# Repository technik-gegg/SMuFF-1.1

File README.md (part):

# Welcome to the SMuFF project

Here's the official firmware package for the **S**mart **Mu**lti **F**ilament **F**eeder, as published on [Printables](https://www.printables.com/de/model/194737-smuff-v6-smart-multi-filament-feeder-with-bondtech) and [Thingiverse](https://www.thingiverse.com/thing:3431438). Read the full story on how it came to life on my official [SMuFF homepage](https://sites.google.com/view/the-smuff/).

If you like this project and find it useful, you may consider [donating](https://sites.google.com/view/the-smuff/downloads/assembly-manual#h.m5ewgcp0jfk6).

To use this firmware, you have to [compile it](https://sites.google.com/view/the-smuff/how-to/tutorials/compile-the-firmware?authuser=0) and flash it to one of these (already supported) controller boards:

| Board |  |
|------------|-----|
| Bigtreetech [SKR mini E3 V3.0](https://www.biqu.equipment/products/bigtreetech-skr-mini-e3-v2-0-32-bit-control-board-for-ender-3) |**recommended** |
| Bigtreetech [SKR mini E3-DIP V1.1](https://www.biqu.equipment/products/bigtreetech-skr-e3-dip-v1-0-motherboard-for-ender-3)||
| Bigtreetech [SKR mini E3 V2.0](https://www.biqu.equipment/products/bigtreetech-skr-mini-e3-v2-0-32-bit-control-board-integrated-tmc2209-uart-for-ender-4) ||
| Bigtreetech [SKR mini V1.1](https://www.biqu.equipment/collections/control-board/products/bigtreetech-skr-mini-v1-1-motherboard-32-bit-arm-equipped-with-tmc2208-v2-1-tmc2130-spi-driver-stepstick-for-3d-printer-desktop?variant=20361870377058)||

The Bigtreetech SKR mini series boards are very small and yet powerful because of the 32-Bit STM Microcontroller Unit.

Of course, this firmware can also be configured to run on any other controller board, as long as it meets the specifications. Although you might be able to utilize older 8 bit boards, I don't recommended it - you'll most probably run out of memory (Flash/RAM) very soon. I recommend using a 32 bit controller board instead.
Make sure your board of choice has at least **256K** of Flash memory, **48K** of (S)RAM and all other components needed, which are at least:

+ two stepper motor drivers (sockets)
+ two endstop connectors
+ one servo connector (or two spare I/O pins for Software-I2C)
+ an onboard SD-Card
+ one spare serial port (USB or TTL)
+ a 128 x 64 pixel display connector
+ a rotary encoder connector

Simply create a new build environment in your **platformio.ini** and adopt the settings according to your controllers hardware in your custom **pins.h** file.

The configuration files **\*.json** and **debug.txt** have to be copied into the root folder of your SD-Card for the controller board. Hence, changing runtime parameters doesn't require recompiling the firmware. Just edit the settings from within the built-in menus or the [WebInterface](https://github.com/technik-gegg/SMuFF-WI), save them and reboot.

I've added the option to run GCode scripts for automated testing of your hardware.
In the **test** folder you'll find some sample scripts. Copy the folder over to your SD-Card and pick a script from within the menu to start the test run. Once started, the test will run infinitelly until you stop it.
Each test result will be displayed on the LCD and also sent to the log serial port (which is the USB port, if not defined otherwise).

For more information about building the SMuFF and some more detailed stuff, head over to my official [SMuFF homepage](https://sites.google.com/view/the-smuff/) or to my [Discord server](https://discord.com/invite/BzZ3rBf).

---

## Credit where credit is due

A special thanks to the folks who have created the following (Arduino) libraries, on which the SMuFF firmware builds upon:

+ [Adafruit](https://github.com/technik-gegg/Adafruit-PWM-Servo-Driver-Library.git) for the PWM Servo library
+ [Benoît Blanchon](https://github.com/bblanchon/ArduinoJson.git) for the Arduino JSON library
+ [Bill Greinman](https://github.com/greiman/SdFat) for the SD-Card library
+ [Oliver Kraus](https://github.com/olikraus/U8G2_Arduino.git) for the U8G2 display library
+ [teemuatlut](https://github.com/teemuatlut/TMCStepper) for the TMC-Stepper library
+ [the creators of the](https://github.com/technik-gegg/SoftWireSTM32/) SoftWireSTM32 library
+ [Tom Schimansky](https://github.com/TomSchimansky/CustomTkinter) for the Custom Tkinter Python package
+ [Akash Bora](https://github.com/Akascape) for the CTkMessagebox and CTkToolTip packages

---

## Recent changes

**3.25** - minor fixes/changes

+ restricted scanning of the I2C bus to valid slave addresses (0-7 and 120-127 are reserved addresses). Although this didn't cause any error yet, it could have caused some unwanted effects in the future.
+ added a new option to route debug messages to other than the default Serial 2 (a.k.a. TFT-Header): Create a file in the root folder of the SD-Card named:
  + **dbg2usb.txt** for Serial 0 (a.k.a. USB)
  + **dbg2exp.txt** for Serial 1
  + **dbg2oth.txt** for Serial 3

   **Keep in mind:** These files need no content. Not every port (except USB) is available on every board, it depends on board and configuration. To reset sending debug messages to default Serial 2, delete or rename the file.
+ added the **Adafruit Stepper + DC Motor FeatherWing** board as a 2nd option for the Spool-Rewinder controller. To use it, you have to define **USE_SPOOLMOTOR_FEATHERWING** in addition to **USE_SPOOLMOTOR** in the *config_defaults* and/or tick the according option in the *Firmware Build Configurator*.

**3.24** - added new "Firmware-Build Configurator"

+ made the build configuration easier by adding a custom dialog (Python/Ctk). Now, the *PROJECT TASKS* treeview only contains the basic build environments for each supported controller. Everything else can now be configured right after clicking on the **Build** task using this dialog:

This is by far more convenient than parsing through the *platformio.ini* or trying to find the build environment you want.
Tooltips will show up when hovering over the checkboxes, which briefly explain why you would use this option.
After the build you'll find a **readme-build.txt** file in the output folder, listing the options that have been set for this particular build.
To define a set of **personalized default settings** depending on the controller used, one can list them under the *config_defaults* section in *platformio.ini*.
*Please be aware that for using this feature, PlatformIO needs to install some Python packages once. This happens automatically at your very first build.*
+ updated SdFat library reference to 2.2.0
+ added the option to use the "old" clock settings (those recommended by STM) for the SKR E3 V3.0 board instead of the new ones introduced in version 3.23.
+ added a couple more debug messages while the firmware is being initialized.

**3.23** - bugfix, Motorized Spool Rewinder option added

+ fixed the bug that caused some (newer) SKR E3 V3.0 boards not being recognized (enumerated) when connected via USB.
+ added **_SPM** build environments, which allow utilizing the [Motorized Spool Rewinder](https://sites.google.com/view/the-smuff/how-to/build/the-spool-rewinder). To use this option, you have to copy the *help* and *menus* folders to your SMuFFs SD-Card. Also, please notice the added content in **MATERIALS.json**.
+ added GCodes **M3**, **M4** and **M5** to allow controlling the spool motors of the *Motorized Spool Rewinder*.

**3.22** - reorganized Build Environments

+ reorganized Build Environments as announced in 3.21.
.
+ added include of <stdint.h> to SMuFF.h, since latest builds seem to fail.

**3.21** - some changes based on the previous release

+ reworked the Build Environments in **platformio.ini**
 Since the **SKR E3 V3.0** has become the most dominant contoller board and the others are getting more and more outdated, I've decided to get rid of some of the Build Environments for "older boards" and add all the possible permutations for the E3 V3.0 instead. The suffixes are meant to be self-explanatory but as a hint: **NPX** means NeoPixels (on tools), **MS** means Multiservo and **DDE** means Direct Drive Extruder.
 Here's what the *PROJECT TASKS* treeview in VSCode now looks like:
 
 Simply open the Build Enviroment that matches your setup and click on "Build".
 Outdated Build Environments are still contained in the ini-file but need to be un-commented in order to make them show up in the *PROJECT TASKS* treeview.
+ the (FYSECT / BTT / MKS) **MiniPanel 12864 V2.1** display has become the default option now. It's the cheapest and easiest to source display, so I declared it the "standard".
+ while playing around with the new behaviour of **USE_NUM_PIXELS** introduced in the previous release, I figured, it's far easier to have the number of LEDs configurable at runtime and thus, I've moved it to the SMuFF configuration file. Hence, this definition is now gone from the platformio.ini!
When you update to this version, please keep in mind to also copy the new **display.mnu** and **m205.txt** to your SMuFF's SD-Card, into the folders *menu* and *help* accordingly.
+ I also found an unpleasant but logical behavior in the *Marquee* animation when more than 7 LEDs are in use: It skips LEDs because on the beatsin() calculation and BPM settings, so I fixed that.
+ while I was at it, I also added two new Idle-Animations: Rainbow and Cylone. Thus, you need to copy the **anim-type.opt** to the *options* folder as well. Then pick the one that you fancy the most from the *Display menu*.

**3.20** - small feature change

+ corrected the behaviour of the **USE_NUM_PIXELS** definition in *platformio.ini*. This defines how many **NeoPixel LEDs** one plans to use for one tool (which usually is: "1 LED per tool").
This feature comes in handy when you're using a NeoPixel strip with a higher density. The "standard" NeoPixel strips come with a density of 60 LEDs/meter but they're also available in 30, 72, 96, 144, 240 or even 332 LEDs/m.
It turned out, that on strips with **144 LEDs/m** the LED spacing is around 7mm (i.e. 1000/144 = 6.94), which corresponds to 3 LEDs for 21mm! Coincidentally, this is also the exact width of one Filament-Guide. Hence, using a 144 LED/m strip saves you from the tedious job of cutting a strip and re-soldering the LEDs in order to get them into the right position. Simply use a longer strip (3 LEDs * number_of_tools) and set **USE_NUM_PIXELS** to 3 before compiling the firmware.

**3.19** - bug fix

+ fixed bug in Selector homing. When homed, SMuFF wasn't able to select tools because the Selector endstop was still triggering.

**3.18** - minor bug fix

+ fixed bug in displaying menu items

**3.17** - minor bug fixes / optimizations

+ fixed bug in platformio.ini for SKR Mini environment.
+ fixed bug in *NeoPixels on Tools*, if more than 5 tools are being used. Init of the NeoPixels happened before the Config was read and hence the count of tools/NeoPixels was incorrect.
+ optimized code for the steppers (*ZStepperLib*) yet again. The *isrStepperTimerHandler()* method now has an overall runtime of about **15uS** on a **STM32F1** MCU running at 72MHz.
+ changed some methods in timers.h/timers.cpp in order to shave off some microseconds in processing time.
+ fixed bug in synchronous movement of the steppers. Feeder stepper wasn't moving at the same pace as the DDE Feeder.
+ changed the USB signature to **STMicroelectronics SMuFF 3.x**. This way it's easier to distinguish which controller is for the SMuFF on the Raspberry Pi.
+ added meaningfull description headers to all methods in *ZStepperLib*, so it can be reused in other projects.
+ moved hardware Debug-Pin for E3-DIP controller from **Y-STOP** to **SWCLK** for a cleaner wave form. Since this is for my debugging only, you don't have to care much about this change.
+ removed TMC library and build flags from **E3-DIP** and **SKR MINI**, since those boards have no native TMC support (i.e. not being controlled through serial or SPI) and hence TMC drivers are running in "Standalone" a.k.a. "A4988" mode.
+ modified the **Acceleration Distance** behaviour. If this value is set to **0**, SMuFF will use 20% of the total distance for accel/decel, which results in a somewhat smoother acceleration/deceleration.
+ fixed bug stepper movement not stopping on endstop trigger. For some (still undiscovered) reason, the endstop ISR doesn't fire while steppers are moving.
+ changed/removed a couple of debug messages to make them a bit more meaningful.

**3.16** - bug fixes / enhancements / cleanup

+ **changed the stepper motors timer prescaler from 24Mhz to 2MHz** (internally 4MHz). This means, you **must** adjust your stepper ticks, otherwise steppers are going to turn terribly slow! Had to do this in order to gain more granular control over the stepper motors at lower speeds.
*Rule of thumb: Divide your current speed settings (Max. speed, Accel. speed, Purge speed, etc.) roughly by 10.*
The stepper timer in fact is running on double the frequency (4MHz) in order to achieve a longer pulse on the stepper driver, because now every 1st tick is used to set the STEP signal, every 2nd to reset the STEP signal. This makes the *Step-Delay* setting unnecessary and you should set it to 0. Though I left this setting in the config, just in case one needs it.
+ changed behaviour of "Unload retraction". If a value is set, it will only be executed if filament is fully loaded (down to nozzle). Keep in mind that this feature is used to shorten the filament remains when using the Cutter and yet only works on a Bowden setup.
+ changed data-type in *purgeFilament()* from uint16_t to double for more accurate purging.
+ changed the method of debug outputs in endstop interrupt functions, since sending data to serial ports from within ISR routines is always a bit critical and may block or crash the controller.
+ added **DEV4** debug flag for a more granular output control of debug messages (i.e. printing incoming GCodes, memory stats, ...).
+ updated GCode **M100** to determine free system memory (RAM). Before, this GCode only returned "ok".
+ added printing out memory stats every minute if *DEV4* debug flag is set.
+ removed the "*Mirroring the display on a VT-100 terminal*" feature introduced in V2.24 completely. Although it was nice to have back then, the software options around the SMuFF have evolved. Hence this feature is obsolete now and was only messing up the source code.
+ removed the (meanwhile) obsolete conditional code for FastLED library. My modified Adafruit NeoPixel library is covering all that's needed.
+ overhauled the code for handling the NeoPixels on tools. NeoPixels will not update as long as one of the stepper motors is spinning (Feeder / Selector), which makes the steppers run smoother.
+ added parameter **P** to GCode **M700** (load filament) in order to purge material (after it's being loaded). If no *value* (e.g. *M700 P*) is given, it'll purge the configured purge amount, otherwise the length of filament given in *value* (e.g. *M700 P12.34*).

  **[ Bug fixes ]**

+ fixed the bug that puts a "loading" dialog on the display while in *Testrun mode* (kudos to **palkovnik807**).
+ fixed the bug where retries were not being decremented while unloading filament (a.k.a "infinite loop" if unloading went wrong).
+ fixed a potential buffer overflow in *drawPurgingMessage()* and *printPeriodicalState()* functions.
+ fixed a bug that may have caused the MS1/MS2/MS3 pins being set up wrong on the **E3-DIP V1.1** (only), because the according pins on the MCU were in an undefined state. Now those pins are being set to LOW (0V) at startup.

**3.15** - minor changes / bug fixes

+ added option **NEVER_DISABLE_SERVOS** in *platformio.ini* section *'other'* which will inhibit disabling servos after they had been moved. The default behaviour is that the SMuFF will disable the PWM signal on **Wiper** and **Cutter** servos after wiping/cutting, because some servos run less jittery when disabled.
However, it turned out that disabling the PWM signal on some servos causes those servos eventually start moving out of the blue. Allowing the PWM signal to stay active helped fixing this issue.
If you discover random movements on your Wiper/Cutter servo, activate this new option before compiling the firmware.
*This option however doesn't influence the behaviour on the Multiservo board(s) - which still are the better option for driving servos.*
+ fixed the bug that sometimes caused the filament not being fully retracted (i.e. Feeder endstop not triggered). Happens only if the configured "Bowden length" value doesn't match the real distance or the filament "slipped" during retraction. In such case the Feeder was supposed to retry until the endstop has triggered but didn't due to wrong condition checking. Thanks to **palkovnik807** on Discord for pointing it out.
+ fixed the bug that caused the **DDE Feeder** not doing a purge under certain conditions because the stepper wasn't enabled. Thanks to **Thyom** on Discord for finding it.
+ added printout of DDE Feeder endstop state for GCode **M119**, in case SMuFF is configured for DDE.

**3.14** - minor changes / bug fix

+ added option **USE_NUM_PIXELS** in *platformio.ini*. Usually, the number of Neopixels matches the number of tools but in some special case you may have more Neopixels on your strip then tools. In order to make the animations using all pixels, enable this definition and set its value to the according number.
+ fixed bug where Lid servo didn't close before unloading when Cutter has been configured as sitting "on top".

**3.13** - Changes for Duet3D and Serial display / some bugfixes

+ fixed bug in TMC driver **Stealth-Mode setting** via SMuFF-WI. Value was accidentally inverted.
+ fixed bug that caused a compilation failure when using the *SKR_E3_30_RET6___DDE* build environment.
+ added [SMuFF-Backbone](https://sites.google.com/view/the-smuff/work-in-progress?authuser=0#h.m19pbkoy3v6p) schematic and PCB design.
+ added **DuetSerial** (port) setting to **SMUFF.json** and menus. You **must** now define the serial port where the Duet3D/RRF is connected to (set to Ser.1 by default). This serial port will only be taken into account if the SMuFF is configured for Duet3D/RRF. For this option you need to copy the modified **options.mnu** and **duet3d.opt** files into the according folders on your SMuFFs SD-Card.
+ added **DspSerial** (port) setting to **SMUFF.json**. The Display serial port can only be configured either through the **-D DISPLAY_SERIAL_PORT** definition in *platformio.ini* or manually in SMUFF.json but not from the menus (because there will be no menus in this mode). See notes on **USE_SERIAL_DISPLAY** for version **3.00** down below.
+ updated **M42** & **M280** & **M205** help files (for Multiservo use).
+ added Dialogs and Sound support on SMuFF-WI when *USE_DISPLAY_SERIAL* is enabled.
+ added **SWAP_SELECTOR_ENDSTOP** build option for those who experience the X-STOP (used for Selector) is not being triggered on a **SKR E3 V3.0**. With this option enabled, the firmware expects the Selector endstop to be connected to *Y-STOP* rather than *X-STOP*.
+ added *JAM* flag in periodical status messages; This is being used in my OctoPrint/Klipper plugins to indicate whether or not the tool change has failed for some reason.
+ added option to switch the *Debugger Serial Port* from within **debug.txt** on startup, without the need for recompiling the firmware. To use this option simply add a **;x** after the value, whereas *x* determines a port number between **0** and **3**. Port **0** always indicates the **USB** serial port, whereas ports **1..3** depend on the controller board you're using (*port 2 is the default value and is assigned to the **TFT** header on most boards*).
*Keep in mind:* This setting will vanish once you set the debug flags via GCode **M111** and store them using **M500**.
+ added option to switch the *Debugger Serial Port* on the fly via **M205** GCode. To use it, simply apply parameters **P"ChangeDbg" Sx**, whereas *x* is the number of the new serial port in the range of **0..3** (see description above).
*Keep in mind:* This setting is temporary and will be reset at the next boot.
+ added option to filter in help files. After the **?** append the phrase to filter for. For example: **M205?dist** will only show the header and all lines containing the string *"dist"*.

**3.12** - Changes for the MULTISERVO option

+ reworked **MULTISERVO** option. For one it's now named *USE_MULTISERVO* for more consistency throughout the other options. For the other, it's now being used to configure all servos to control them via an external board (Adafruit Multiservo/FeatherWing/ [SMuFF-Backbone](https://sites.google.com/view/the-smuff/work-in-progress?authuser=0#h.m19pbkoy3v6p) board). This external board is always being controlled by using software I2C. The pins used for SW-I2C vary throughout the different controller boards.
+ the **USE_MULTISERVO** flag will become more importance in the future, hence I moved that option to the *[other]* section of *platformio.ini*.
+ modified the external **SoftWireSTM32 library** which had a bug that caused that the library wasn't able to scan for devices on the I2C bus properly.
+ moved relay control pin on **SKR mini E3-DIP V1.1** from **MS3** pin of the Z-Axis driver socket (in DDE mode) to the **TH0** pin if the **USE_MULTISERVO** flag is set. This is because this signal is being used as the data pin (SDA) for the software I2C controlling the Adafruit Multiservo board.
+ added **USE_MULTISERVO_RELAY** flag to the compile options in order to control the relay via output #5 on the Multiservo board instead of *MS3*, *TH0* or *PROBE* pins. This will be the future method of controlling the relay switch. **Please notice:** This method requires a pull-up resistor of 4.7K - 10K, either on +5V or +3.3V to make the signal switch as intended. The reason being is that the outputs on the Multiservo board are configured as open-drain.
+ corrected build environment for **SKR mini V1.1** (FastLED library was still referenced instead of the Adafruit Neopixel library).
+ fixed the bug that caused the **SKR mini V1.1** to hang at startup (wrong *debugSerial* port has been initialized).
+ added a couple more meaningful error messages to the GCode interpreter.
+ changed **SERVOMAP.json** config file to reflect the new MUTISERVO options. Please copy this file over to your SMuFF's SD-Card.
+ changed **ServoMinPwm** and **ServoMaxPwm** settings in SMUFF.json. These settings work better with the Multiservo boards. Copy the modified file over to your SMuFF's SD-Card and don't forget to reconfigure your servo angle settings.
+ added the two user controlled servo ports (USER1/USER2) to **M280** GCode and **M42** GCode when using the MULTISERVO option. Send M280 P1000 / P1001 if those ports are supposed to drive custom servos, or M42 P1000 / P1001 if those ports are configured to be used as output pins (i.e. to be switched on/off).
+ added **M260** GCode to allow scanning for I2C devices at runtime using the GCode interface.
+ updated some of the KiCad files to KiCad version 6.x

**3.11** - Some minor changes

+ added flashing of the "Periodical State sending" glyph on the display when it's enabled. Flashing happens at half the frequency of states being sent.
+ added current relay state (**E** / **I**) to "Periodical States".
+ changed output of **M122W** and **M503W**. *M122W9* and *M503W0* are now sending all state/configuration data at once, which makes SMuFF-WI connect faster.

**3.10** - Some minor changes / bug fixes

+ **removed SKR E3 V1.2** from the list of supported devices because this board isn't optimal for the SMuFF V6. Consider moving to E3 V2.0 or better E3 V3.0.
+ changed some default settings in *SMUFF.json* which fits better for V6 default configuration.
+ switched from FastLED to AdafruitNeoPixel library throughout for all boards.
+ fixed bug where DDE extruder wasn't reading out the endstop while retracting.
+ fixed bug with NeoPixel refresh.
+ added dedicated timer for NeoPixel refresh because the existing solution interfered with servos and steppers.
+ (re-) added timer for servos because the existing solution interfered with the stepper timer.
+ changed timer priorities and intervals to get rid of servo jitter.
+ changed priority on timers, so the stepper timer (and thus the stepper movement) is a bit more agile now.
+ added GCode command **M155** for fast switching of *sending periodical status messages*.
+ GCode **M205 help file** updated.
+ cleaned up *platformio.ini* by extending environments in *__DDE.
+ added GCode command **M562** to reset a *Feeder Jam* remotly.
+ added more status/error responses in order to make the Klipper module run smooth
+ added feeder states (SPL in periodical states) for all variants. This value is now (lower nibble: Splitter, upper nibble: non-Splitter):
  + 0x00 means *not loaded*
  + 0x01 means *loaded to Splitter*
  + 0x02 means *loaded to Nozzle*
  + 0x10 means *loaded to Selector*
  + 0x20 means *loaded to Nozzle*
  + 0x40 means *loaded to DDE*
+ added "JAMMED" state on display when feeder is being jammed

**3.00** - Moving from Maple to Arduino Core STM32 framework  

+ ported firmware from **Maple** to new **Arduino Core STM32** (stm32duino) framework in order to make boards with different MCUs available. This version is still compatible with the predecessor SKR controller boards, such as the SKR Mini/E3-DIP/V2.0.
+ added **debug.txt** to define the amount of debug messages being spit out without re-compiling the firmware. Also added the option of changing the debug level through GCode, which is **M111**. See *M111?* for details.
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
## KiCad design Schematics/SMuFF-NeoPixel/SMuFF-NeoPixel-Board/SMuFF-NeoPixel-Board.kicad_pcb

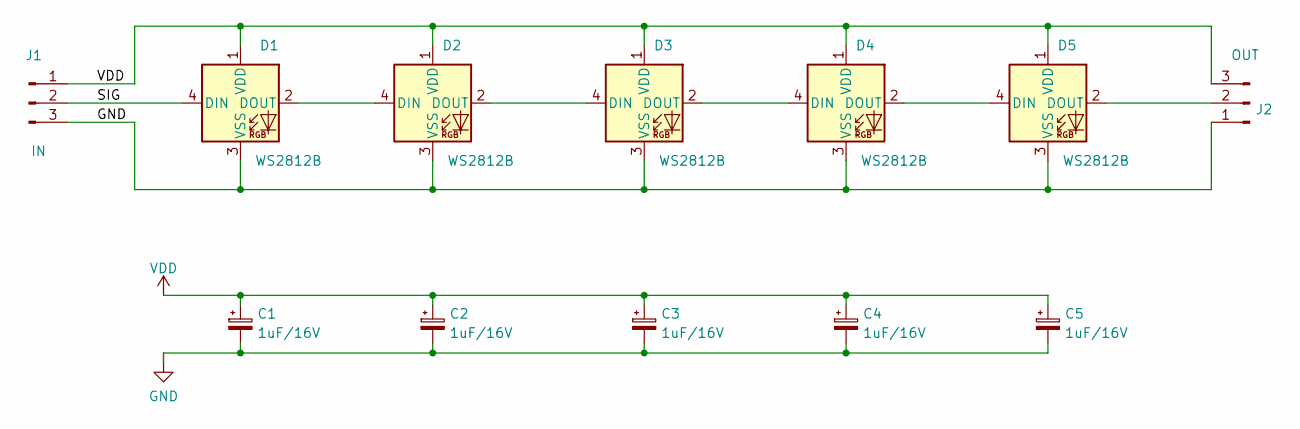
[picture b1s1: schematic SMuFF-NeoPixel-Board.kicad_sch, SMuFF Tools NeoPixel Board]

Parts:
C1, C2, C3, C4, C5: 1uF/16V; CP_EIA-2012-12_Kemet-R
D1, D2, D3, D4, D5: WS2812B; LED_WS2812B_PLCC4_5.0x5.0mm_P3.2mm
J1: IN; PinHeader_1x03_P2.54mm_Vertical_SMD_NeoPixel
J2: OUT; PinHeader_1x03_P2.54mm_Vertical_SMD_NeoPixel

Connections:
/SIG: D1.4 (DIN), J1.2
GND: C1.2, C2.2, C3.2, C4.2, C5.2, D1.3 (VSS), D2.3 (VSS), D3.3 (VSS), D4.3 (VSS), D5.3 (VSS), J1.3, J2.1
unnamed: D1.2 (DOUT), D2.4 (DIN)
unnamed: D2.2 (DOUT), D3.4 (DIN)
unnamed: D3.2 (DOUT), D4.4 (DIN)
unnamed: D4.2 (DOUT), D5.4 (DIN)
unnamed: D5.2 (DOUT), J2.2
VDD: C1.1, C2.1, C3.1, C4.1, C5.1, D1.1 (VDD), D2.1 (VDD), D3.1 (VDD), D4.1 (VDD), D5.1 (VDD), J1.1, J2.3

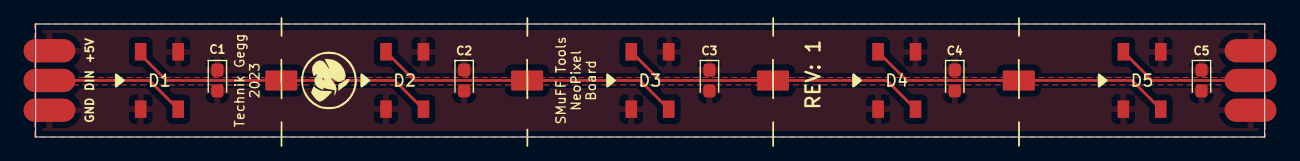
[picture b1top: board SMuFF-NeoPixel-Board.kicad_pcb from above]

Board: 2 copper layers, 105.0 x 9.7 mm, 12 parts (0 on the bottom side), 8 nets.

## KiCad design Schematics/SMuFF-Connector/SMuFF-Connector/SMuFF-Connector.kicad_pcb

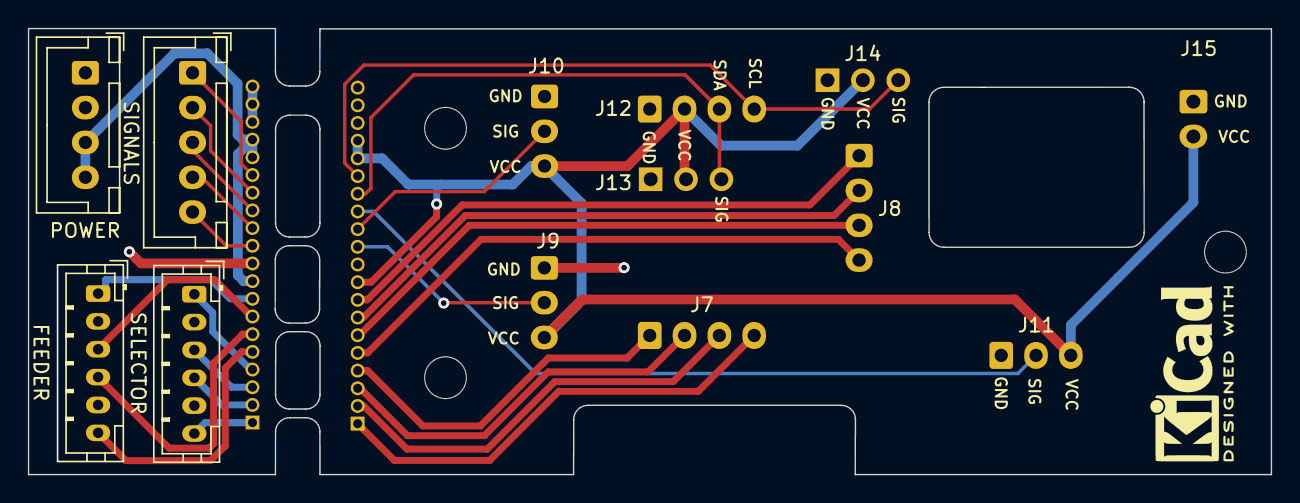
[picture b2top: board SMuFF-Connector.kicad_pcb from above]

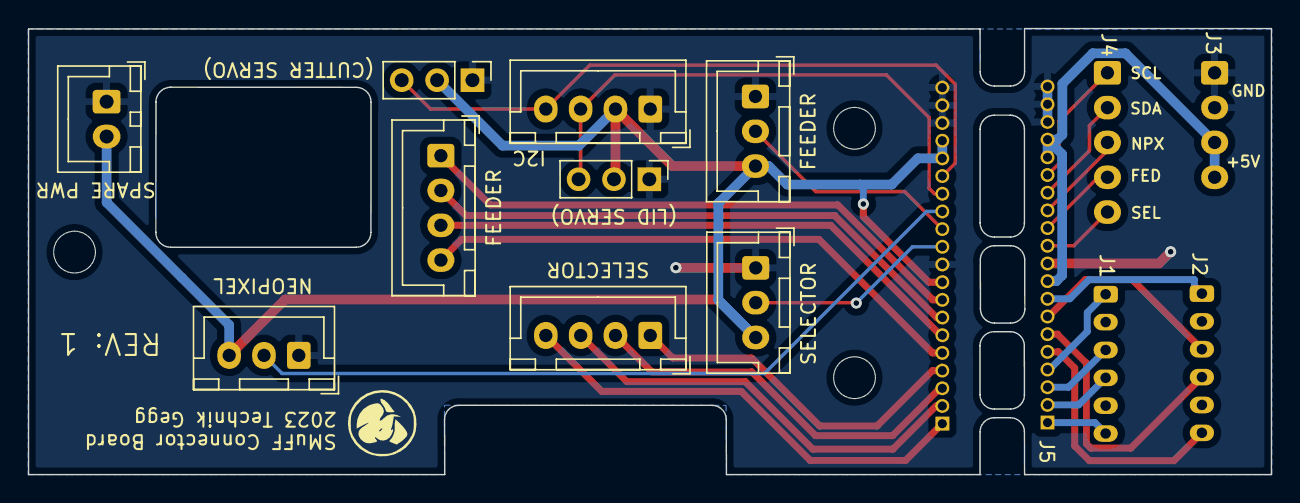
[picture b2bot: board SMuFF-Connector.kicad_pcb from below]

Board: 2 copper layers, 89.2 x 32.0 mm, 18 parts (11 on the bottom side), 29 nets.

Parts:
H1, H2, H3: MountingHole; MountingHole_3mm
J1: Selector Stepper; JST_PH_B6B-PH-K_1x06_P2.00mm_Vertical
J2: Feeder Stepper; JST_PH_B6B-PH-K_1x06_P2.00mm_Vertical
J3: Power; JST_XH_B4B-XH-A_1x04_P2.50mm_Vertical
J4: Signals; JST_XH_B5B-XH-A_1x05_P2.50mm_Vertical
J5: Connector 1x20; PinHeader_1x20_P1.27mm_Horizontal
J6: Conn_01x16; PinHeader_1x20_P1.27mm_Vertical
J7: Selector Motor; JST_XH_B4B-XH-A_1x04_P2.50mm_Vertical
J8: Feeder Motor; JST_XH_B4B-XH-A_1x04_P2.50mm_Vertical
J9: Selector Endstop; JST_XH_B3B-XH-A_1x03_P2.50mm_Vertical
J10: Feeder Sensor; JST_XH_B3B-XH-A_1x03_P2.50mm_Vertical
J11: NeoPixels; JST_XH_B3B-XH-A_1x03_P2.50mm_Vertical
J12: I2C; JST_XH_B4B-XH-A_1x04_P2.50mm_Vertical
J13: (Lid Servo); PinHeader_1x03_P2.54mm_Vertical
J14: (Cutter Servo); PinHeader_1x03_P2.54mm_Vertical
J15: SPARE; JST_XH_B2B-XH-A_1x02_P2.50mm_Vertical

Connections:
+5V: J6.9, J6.16, J6.17, J9.3, J10.3, J11.3, J12.2, J13.2, J14.2, J15.2
/Feeder: J4.4, J5.12
/NeoPixel: J4.3, J5.13
/SCL: J4.1, J5.15
/SDA: J4.2, J5.14
/Selector: J4.5, J5.11
/VCC-IN: J3.3, J3.4, J5.9, J5.16, J5.17
GND: J3.1, J3.2, J5.10, J5.18, J5.19, J5.20, J6.10, J6.18, J6.19, J6.20, J9.1, J10.1, J11.1, J12.1, J13.1, J14.1, J15.1
unnamed: J1.1, J5.4
unnamed: J1.3, J5.3
unnamed: J1.4, J5.2
unnamed: J1.6, J5.1
unnamed: J2.1, J5.8
unnamed: J2.3, J5.7
unnamed: J2.4, J5.6
unnamed: J2.6, J5.5
unnamed: J6.1, J7.4
unnamed: J6.2, J7.3
unnamed: J6.3, J7.2
unnamed: J6.4, J7.1
unnamed: J6.5, J8.4
unnamed: J6.6, J8.3
unnamed: J6.7, J8.2
unnamed: J6.8, J8.1
unnamed: J6.11, J9.2
unnamed: J6.13, J11.2
unnamed: J6.12, J10.2
unnamed: J6.14, J12.3, J13.3
unnamed: J6.15, J12.4, J14.3

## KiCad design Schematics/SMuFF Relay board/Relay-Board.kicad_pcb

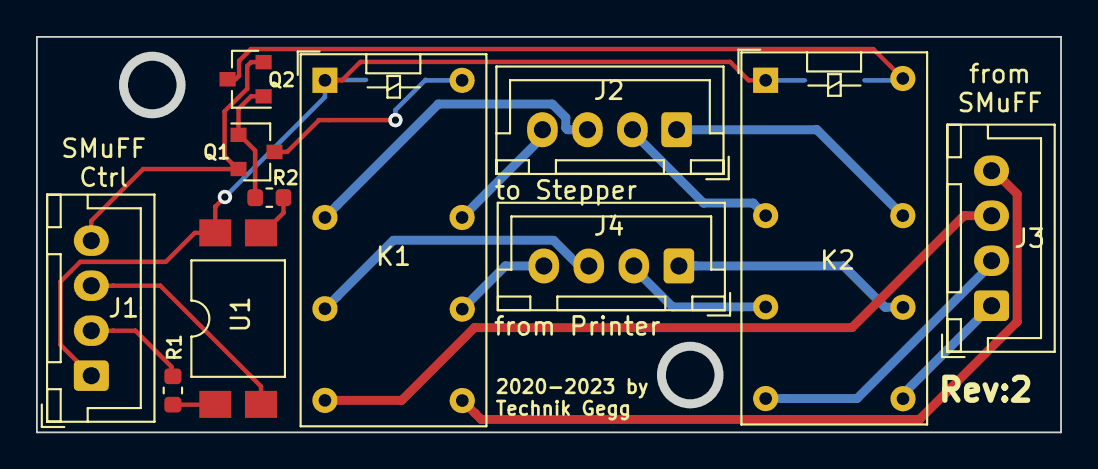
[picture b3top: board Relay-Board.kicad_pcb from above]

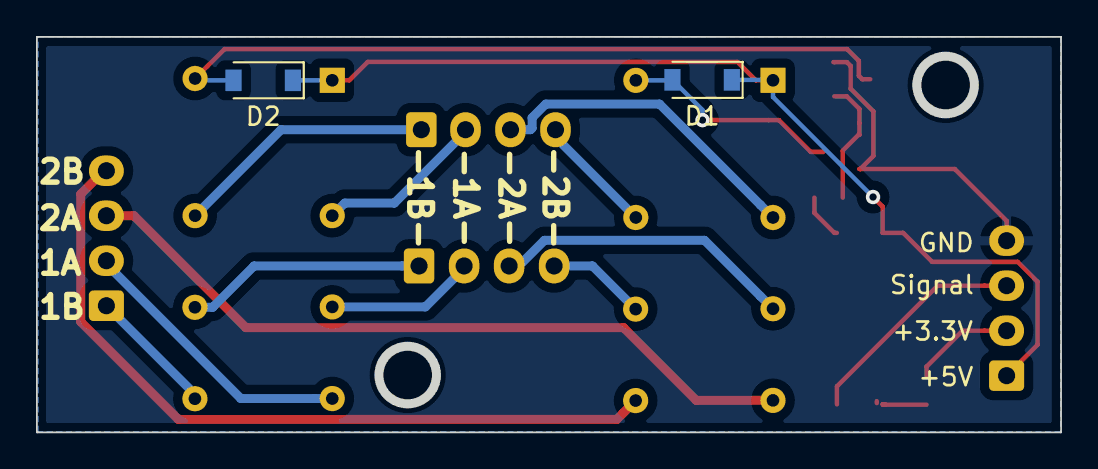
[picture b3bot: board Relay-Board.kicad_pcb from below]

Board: 2 copper layers, 56.9 x 22.0 mm, 13 parts (2 on the bottom side), 21 nets.

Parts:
D1, D2: 1N4148; D_SOD-123
J1, J2, J3, J4: JST XH; JST_XH_B4B-XH-A_1x04_P2.50mm_Vertical
K1, K2: G6A-274P; Relay_DPDT_Omron_G5V-2
Q1, Q2: BC847/547; SOT-23
R1: 390R; R_0603_1608Metric
R2: 1K; R_0603_1608Metric
U1: TLP521; SMDIP-4_W9.53mm_Clearance8mm

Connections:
unnamed: D1.1, D2.1, J1.1, K1.1, K2.1, U1.4
unnamed: D1.2, K1.16, Q1.3
unnamed: D2.2, K2.16, Q2.3
unnamed: J1.2, R1.1
unnamed: J1.3, U1.2
unnamed: J1.4, Q1.2, Q2.2
unnamed: J2.1, K2.13
unnamed: J2.2, K2.4
unnamed: J2.3, K1.4
unnamed: J2.4, K1.13
unnamed: J3.1, K2.9
unnamed: J3.2, K2.8
unnamed: J3.3, K1.8
unnamed: J3.4, K1.9
unnamed: J4.1, K2.11
unnamed: J4.2, K2.6
unnamed: J4.3, K1.6
unnamed: J4.4, K1.11
unnamed: Q1.1, Q2.1, R2.1
unnamed: R1.2, U1.1
unnamed: R2.2, U1.3

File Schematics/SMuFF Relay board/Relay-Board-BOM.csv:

"Source:","D:\Data\PlatformIO\SMuFF\Schematics\SMuFF Relay board\Relay-Board.sch"
"Date:","02.08.2021 17:44:11"
"Tool:","Eeschema (5.1.2)-2"
"Component Count:","13"
"Ref","Value","Footprint","Datasheet","Manufacturer","Vendor"
"D1","1N4148","Diode_SMD:D_0603_1608Metric","https://assets.nexperia.com/documents/data-sheet/1N4148_1N4448.pdf","",""
"D2","1N4148","Diode_SMD:D_0603_1608Metric","https://assets.nexperia.com/documents/data-sheet/1N4148_1N4448.pdf","",""
"J1","JST XH","Connector_JST:JST_XH_B4B-XH-A_1x04_P2.50mm_Vertical","~","",""
"J2","JST XH","Connector_JST:JST_XH_B4B-XH-A_1x04_P2.50mm_Vertical","~","",""
"J3","JST XH","Connector_JST:JST_XH_B4B-XH-A_1x04_P2.50mm_Vertical","~","",""
"J4","JST XH","Connector_JST:JST_XH_B4B-XH-A_1x04_P2.50mm_Vertical","~","",""
"K1","G6A-274P","Relay_THT:Relay_DPDT_Omron_G5V-2","http://omronfs.omron.com/en_US/ecb/products/pdf/en-g6s.pdf","",""
"K2","G6A-274P","Relay_THT:Relay_DPDT_Omron_G5V-2","http://omronfs.omron.com/en_US/ecb/products/pdf/en-g6s.pdf","",""
"Q1","BC847/547","Package_TO_SOT_SMD:SOT-23","http://www.fairchildsemi.com/ds/BC/BC547.pdf","",""
"Q2","BC847/547","Package_TO_SOT_SMD:SOT-23","http://www.fairchildsemi.com/ds/BC/BC547.pdf","",""
"R1","390R","Resistor_SMD:R_0603_1608Metric","~","",""
"R2","1K","Resistor_SMD:R_0603_1608Metric","~","",""
"U1","SFH6206-2","Package_DIP:SMDIP-4_W9.53mm_Clearance8mm","https://toshiba.semicon-storage.com/info/docget.jsp?did=1056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","",""

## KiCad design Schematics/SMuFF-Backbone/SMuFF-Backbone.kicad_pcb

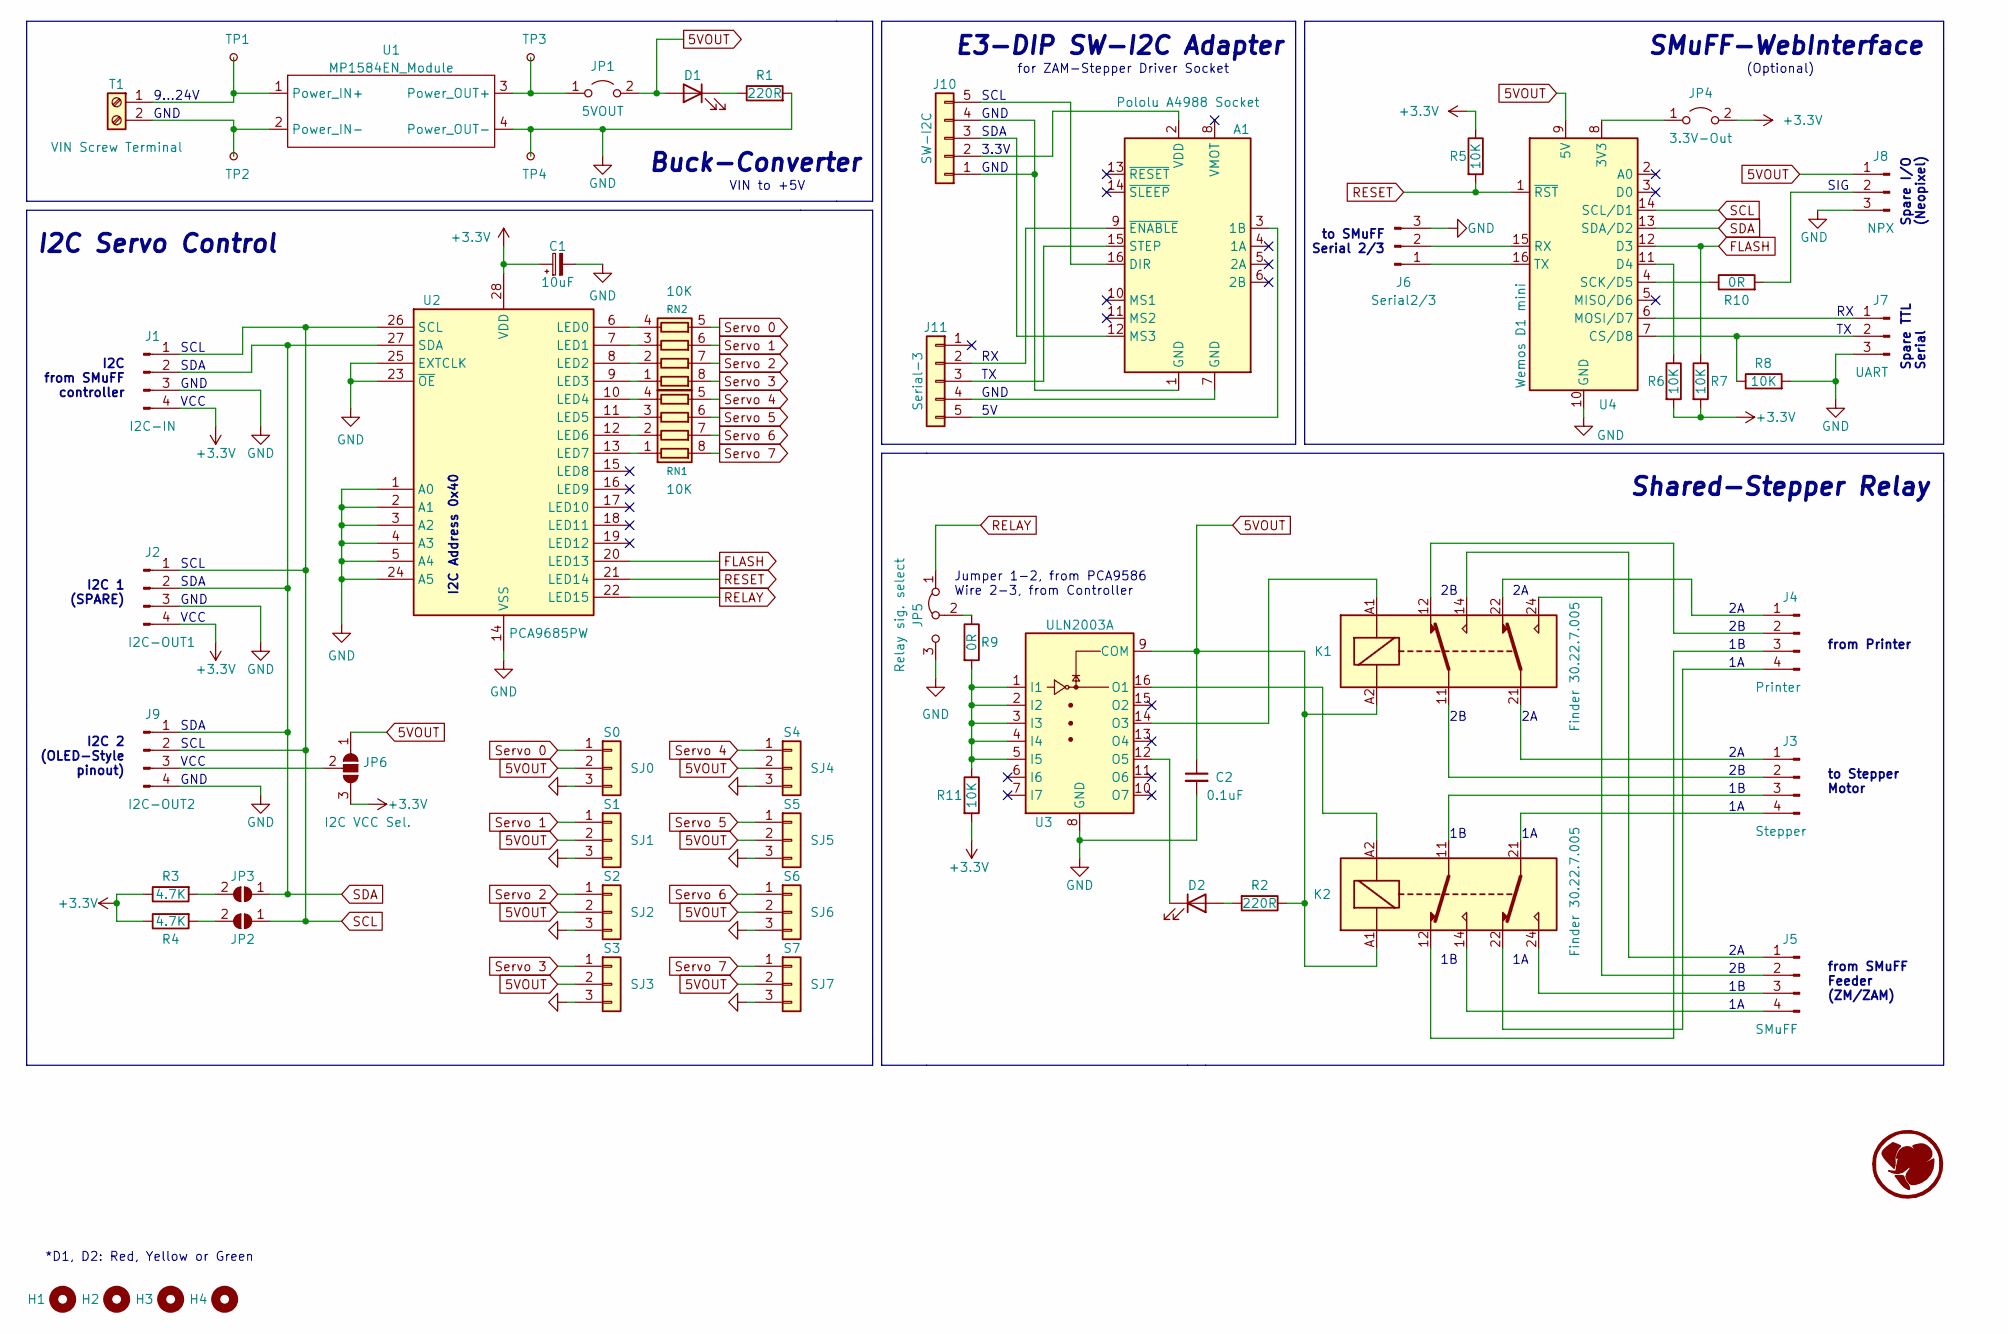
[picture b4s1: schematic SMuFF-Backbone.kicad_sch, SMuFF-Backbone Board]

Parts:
A1: Pololu A4988 Socket; C_1206_3216Metric
C1: 10uF; C_1206_3216Metric
C2: 0.1uF; C_1206_3216Metric
D1, D2: (no value)
H1, H2, H3, H4: MountingHole; MountingHole_3.2mm_M3
J1: I2C-IN; JST_XH_B4B-XH-A_1x04_P2.50mm_Vertical
J2: I2C-OUT1; PinHeader_1x04_P2.54mm_Vertical
J3: Stepper; JST_XH_B4B-XH-A_1x04_P2.50mm_Vertical
J4: Printer; JST_XH_B4B-XH-A_1x04_P2.50mm_Vertical
J5: SMuFF; JST_XH_B4B-XH-A_1x04_P2.50mm_Vertical
J6: Serial2/3; JST_XH_B3B-XH-A_1x03_P2.50mm_Vertical
J7: UART; JST_XH_B3B-XH-A_1x03_P2.50mm_Vertical
J8: NPX; JST_XH_B3B-XH-A_1x03_P2.50mm_Vertical
J9: I2C-OUT2; PinHeader_1x04_P2.54mm_Vertical
J10: SW-I2C; JST_XH_B5B-XH-A_1x05_P2.50mm_Vertical
J11: Serial-3; PinHeader_1x05_P2.54mm_Vertical
JP1: 5VOUT; PinHeader_1x02_P2.54mm_Vertical
JP2, JP3: Jumper; SolderJumper-2_P1.3mm_Open_RoundedPad1.0x1.5mm
JP4: 3.3V-Out; PinHeader_1x02_P2.54mm_Vertical
JP5: Relay sig. select; PinHeader_1x03_P2.54mm_Vertical
JP6: I2C VCC Sel.; SolderJumper-3_P1.3mm_Open_RoundedPad1.0x1.5mm
K1, K2: Finder 30.22.7.005; Relay_DPDT_Finder_30.22
R1, R2: 220R; R_0805_2012Metric
R3, R4: 4.7K; R_0805_2012Metric
R5, R6, R7, R8, R11: 10K; R_0805_2012Metric
R9, R10: 0R; R_0805_2012Metric
RN1, RN2: 10K; R_Array_Concave_4x0603
SJ0: S0; PinHeader_1x03_P2.54mm_Vertical
SJ1: S1; PinHeader_1x03_P2.54mm_Vertical
SJ2: S2; PinHeader_1x03_P2.54mm_Vertical
SJ3: S3; PinHeader_1x03_P2.54mm_Vertical
SJ4: S4; PinHeader_1x03_P2.54mm_Vertical
SJ5: S5; PinHeader_1x03_P2.54mm_Vertical
SJ6: S6; PinHeader_1x03_P2.54mm_Vertical
SJ7: S7; PinHeader_1x03_P2.54mm_Vertical
T1: VIN Screw Terminal; TerminalBlock_bornier-2_P5.08mm
TP1: SY8205-IN+; TestPoint_THTPad_1.5x1.5mm_Drill0.7mm
TP2: SY8205-IN-; TestPoint_THTPad_1.5x1.5mm_Drill0.7mm
TP3: SY8205-OUT+; TestPoint_THTPad_1.5x1.5mm_Drill0.7mm
TP4: SY8205-OUT-; TestPoint_THTPad_1.5x1.5mm_Drill0.7mm
U1: MP1584EN_Module
U2: PCA9685PW; TSSOP-28_4.4x9.7mm_P0.65mm
U3: ULN2003A; SOIC-16_3.9x9.9mm_P1.27mm
U4: Wemos D1 mini; WEMOS_D1_mini_light

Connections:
5VOUT: C2.1, D1.2 (A), J8.1, JP1.2 (B), JP6.1 (A), K1.A2, K2.A1, R2.1, SJ0.2, SJ1.2, SJ2.2, SJ3.2, SJ4.2, SJ5.2, SJ6.2, SJ7.2, U3.9 (COM), U4.9 (5V)
+3V3: C1.1, J1.4, J2.4, JP4.2 (B), JP6.3 (B), R3.1, R4.1, R5.1, R6.2, R7.2, R11.2, U2.28 (VDD)
FLASH: R7.1, U2.20 (LED13), U4.12 (D3)
GND: C1.2, C2.2, J1.3, J2.3, J6.3, J7.3, J8.3, J9.4, JP5.3 (B), R1.2, R8.2, SJ0.3, SJ1.3, SJ2.3, SJ3.3, SJ4.3, SJ5.3, SJ6.3, SJ7.3, TP4.1, U1.4 (Power_OUT-), U2.1 (A0), U2.2 (A1), U2.3 (A2), U2.4 (A3), U2.5 (A4), U2.14 (VSS), U2.23 (~OE), U2.24 (A5), U2.25 (EXTCLK), U3.8 (GND), U4.10 (GND)
unnamed: A1.1 (GND), J10.1, J10.4
unnamed: A1.2 (VDD), J10.2
unnamed: A1.3 (1B), J11.5
unnamed: A1.7 (GND), J11.4
unnamed: A1.9 (~ENABLE), J11.2
unnamed: A1.12 (MS3), J10.3
unnamed: A1.15 (STEP), J11.3
unnamed: A1.16 (DIR), J10.5
unnamed: D1.1 (K), R1.1
unnamed: D2.1 (K), U3.12 (O5)
unnamed: D2.2 (A), R2.2
unnamed: J3.1, K1.21
unnamed: J3.2, K1.11
unnamed: J3.3, K2.11
unnamed: J3.4, K2.21
unnamed: J4.1, K1.22
unnamed: J4.2, K1.12
unnamed: J4.3, K2.12
unnamed: J4.4, K2.22
unnamed: J5.1, K1.14
unnamed: J5.2, K1.24
unnamed: J5.3, K2.24
unnamed: J5.4, K2.14
unnamed: J6.1, U4.16 (TX)
unnamed: J6.2, U4.15 (RX)
unnamed: J7.1, U4.6 (MOSI/D7)
unnamed: J7.2, R8.1, U4.7 (CS/D8)
unnamed: J8.2, R10.2
unnamed: J9.3, JP6.2 (C)
unnamed: JP1.1 (A), TP3.1, U1.3 (Power_OUT+)
unnamed: JP2.2 (B), R4.2
unnamed: JP3.2 (B), R3.2
unnamed: JP4.1 (A), U4.8 (3V3)
unnamed: JP5.2 (C), R9.1
unnamed: K1.A1, U3.14 (O3)
unnamed: K2.A2, U3.16 (O1)
unnamed: R6.1, U4.11 (D4)
unnamed: R10.1, U4.4 (SCK/D5)
unnamed: R9.2, R11.1, U3.1 (I1), U3.2 (I2), U3.3 (I3), U3.4 (I4), U3.5 (I5)
unnamed: RN1.1 (R1.1), U2.9 (LED3)
unnamed: RN1.2 (R2.1), U2.8 (LED2)
unnamed: RN1.3 (R3.1), U2.7 (LED1)
unnamed: RN1.4 (R4.1), U2.6 (LED0)
unnamed: RN2.1 (R1.1), U2.13 (LED7)
unnamed: RN2.2 (R2.1), U2.12 (LED6)
unnamed: RN2.3 (R3.1), U2.11 (LED5)
unnamed: RN2.4 (R4.1), U2.10 (LED4)
unnamed: T1.1, TP1.1, U1.1 (Power_IN+)
unnamed: T1.2, TP2.1, U1.2 (Power_IN-)
RELAY: JP5.1 (A), U2.22 (LED15)
RESET: R5.2, U2.21 (LED14), U4.1 (~RST)
SCL: J1.1, J2.1, J9.2, JP2.1 (A), U2.26 (SCL), U4.14 (SCL/D1)
SDA: J1.2, J2.2, J9.1, JP3.1 (A), U2.27 (SDA), U4.13 (SDA/D2)
Servo 0: RN1.5 (R4.2), SJ0.1
Servo 1: RN1.6 (R3.2), SJ1.1
Servo 2: RN1.7 (R2.2), SJ2.1
Servo 3: RN1.8 (R1.2), SJ3.1
Servo 4: RN2.5 (R4.2), SJ4.1
Servo 5: RN2.6 (R3.2), SJ5.1
Servo 6: RN2.7 (R2.2), SJ6.1
Servo 7: RN2.8 (R1.2), SJ7.1

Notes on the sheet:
SCL
GND
I2C 2 (OLED-Style pinout)
9...24V
I2C from SMuFF controller
Buck-Converter
I2C 1 (SPARE)
Jumper 1-2, from PCA9586 Wire 2-3, from Controller
to Stepper Motor
to SMuFF Serial 2/3
VIN to +5V
I2C Address 0x40
(Optional)
for ZAM-Stepper Driver Socket
from SMuFF Feeder (ZM/ZAM)
SMuFF-WebInterface
Spare TTL Serial
*D1, D2: Red, Yellow or Green
SDA
SIG
VCC
Spare I/O (Neopixel)
3.3V
E3-DIP SW-I2C Adapter
Shared-Stepper Relay
I2C Servo Control
from Printer

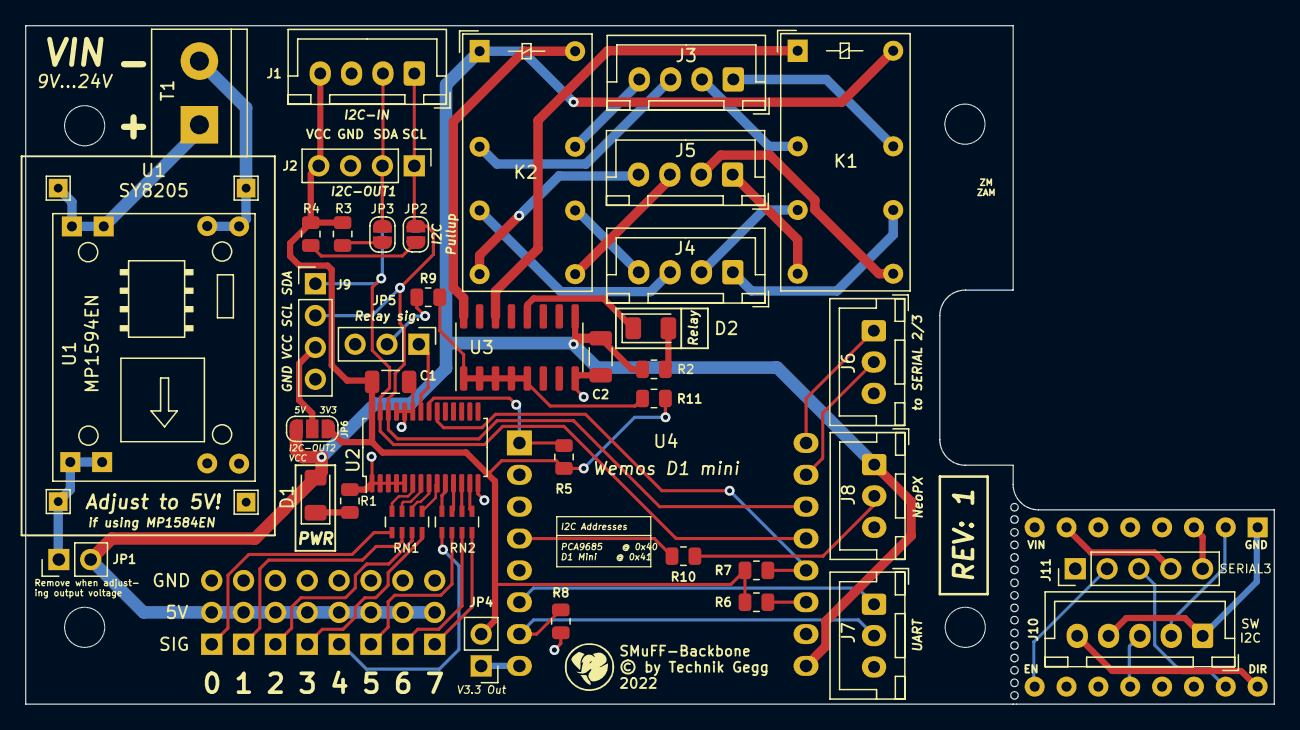
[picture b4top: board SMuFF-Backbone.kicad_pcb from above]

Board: 2 copper layers, 99.6 x 54.1 mm, 58 parts (0 on the bottom side), 65 nets.

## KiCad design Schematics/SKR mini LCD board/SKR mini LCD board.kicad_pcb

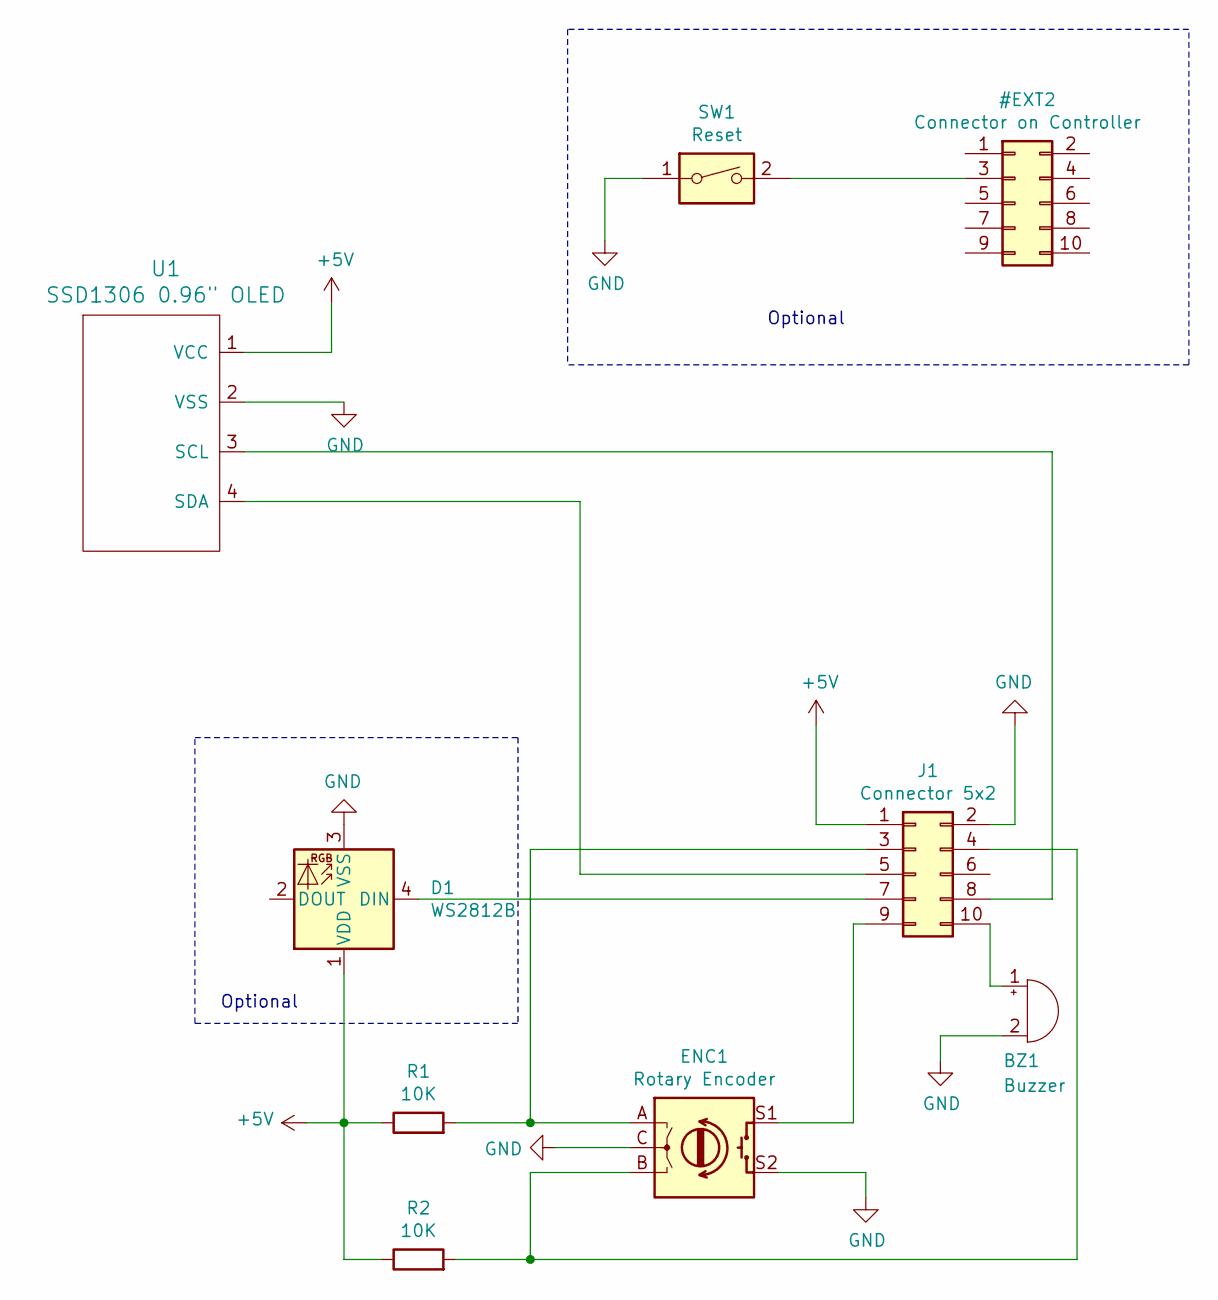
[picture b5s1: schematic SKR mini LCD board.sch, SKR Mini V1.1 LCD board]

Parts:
BZ1: Buzzer; Buzzer_12x9.5RM7.6
D1: WS2812B; LED_WS2812B_PLCC4_5.0x5.0mm_P3.2mm
ENC1: Rotary Encoder; RotaryEncoder_Alps_EC11E-Switch_Vertical_H20mm_CircularMoun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
J1: Connector 5x2; PinSocket_2x05_P2.54mm_Vertical
R1, R2: 10K; R_Axial_DIN0207_L6.3mm_D2.5mm_P10.16mm_Horizontal
SW1: Reset; SW_PUSH_6mm_H7.3mm
U1: SSD1306 0.96\" OLED; PinHeader_1x04_P2.54mm_Vertical

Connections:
+5V: D1.1 (VDD), J1.1, R1.1, R2.1, U1.1 (VCC)
GND: BZ1.2 (+), D1.3 (VSS), ENC1.C, ENC1.S2, J1.2, SW1.1, U1.2 (VSS)
unnamed: BZ1.1 (-), J1.10
unnamed: D1.4 (DIN), J1.7
unnamed: ENC1.A, J1.3, R1.2
unnamed: ENC1.B, J1.4, R2.2
unnamed: ENC1.S1, J1.9
unnamed: J1.5, U1.4 (SDA)
unnamed: J1.8, U1.3 (SCL)

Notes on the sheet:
Optional
Optional

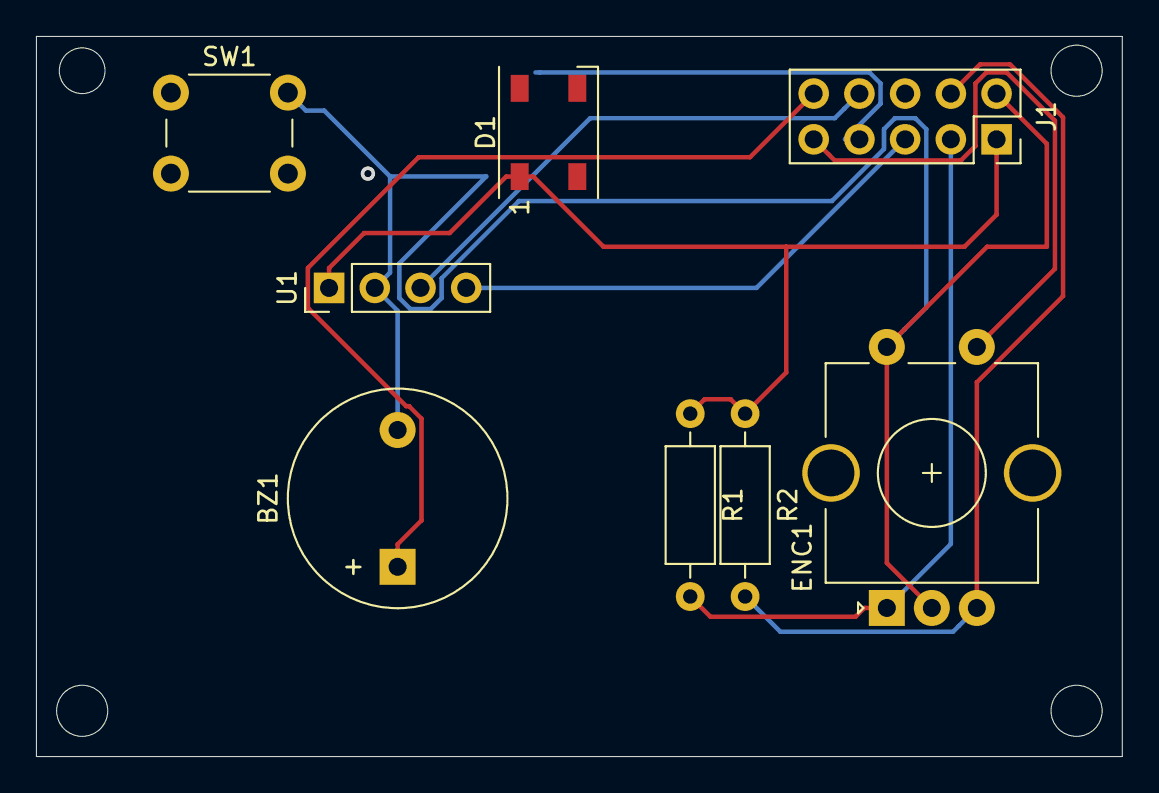
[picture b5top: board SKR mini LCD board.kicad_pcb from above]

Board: 2 copper layers, 60.3 x 40.0 mm, 8 parts (0 on the bottom side), 9 nets.

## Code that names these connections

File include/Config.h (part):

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#define MAX_ERR_MSG             255                 // max. length of error messages

#define NUM_STEPPERS            3
#define SELECTOR                0
#define REVOLVER                1
#define DDE_FEEDER              1
#define FEEDER                  2
#define FEEDER2                 3                   // added for boards with pre-installed stepper drivers

#define MIN_TOOLS               2
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#define SERVO_CUTTER        2
#define SERVO_SPARE1        3
#define SERVO_SPARE2        4
#define RELAY               5
#define SERVO_USER1         6
#define SERVO_USER2         7

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#define POWER_SAVE_TIMEOUT      15      // value in seconds

#if !defined(NUM_LEDS)
#define NUM_LEDS                1       // number of Neopixel LEDS
#define BRIGHTNESS              64
#define LED_TYPE                WS2812B
#define COLOR_ORDER             GRB
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

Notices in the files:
include/Config.h:
Copyright (C) 2019-2024 Technik Gegg
This program is free software: you can redistribute it and/or modify
it under the terms of the GNU General Public License as published by
the Free Software Foundation, either version 3 of the License, or
(at your option) any later version.
Schematics/SMuFF-Backbone/SMuFF-Backbone.kicad_pcb:
© by Technik Gegg
